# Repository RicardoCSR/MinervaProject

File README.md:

# MinervaProject

Registro Mestre de Projeto 

Bases e arquivos de apoio utilizados para o desenvolvimento do projeto:

STM32duino - IDE Arduino Ver.1 e Ver.2

- Fontes TTL 
https://github.com/FrankBoesing/fonts.git
- Display TFT SPI/I2C
https://github.com/Bodmer/TFT_eSPI
- FontConverter - 1
https://rop.nl/truetype2gfx/
- FontConverter - 2
https://oleddisplay.squix.ch/#/home
- RGB888 para RGB565
https://trolsoft.ru/ru/articles/rgb565-color-picker
- App (EM TESTE)
https://thunkable.com/#/

Nixie_Clock - Extensor de Sensores de Sobrevivência

Iniciando em 16/10/2021

Projeto Minerva da paixão pelos clássicos tubos Nixie desenvolvidos na década de 50 aos modernos display LCD, da inspiração veio junto o desafio de unir o antigo ao novo agregando diversos sensores para a apresentação de informações para uso e sobrevivência diário como:

- Pressão (mmHg)
- Temperatura (ºC e F)
- Umidade (%)
- Altitude
- sieverts (µSv e mSv)
- Hora/Data
- Calendário Completo
- Calculadora
- Grandezas e Medidas
- Estação do Ano (Primavera)
- Semana (Semana 39)
- Modo de ajustes dos parâmetros 

Sendo organizados pelos Menus:

Geiger                              - Apresenta Contagem por Segundo, Leitura Sieverts nSv/s
Dosimeter                           - Apresenta valor Dosimetro, Tempo de atualização, faixa de risco de Sv/h
Geiger GF                           - Apresenta gráfico dos valores apresentados nas 24 Horas do Geiger
Calendar                            - Apresenta Calendário
Timer                               - Apresenta Alarme, Contador e Tempo de Volta
Weather GF Temperature              - Apresenta gráfico dos valores apresentados nas 24 Horas do Temperatura
Weather GF Humidity                 - Apresenta gráfico dos valores apresentados nas 24 Horas do Umidade
Weather GF Atmosferic Pressure      - Apresenta gráfico dos valores apresentados nas 24 Horas do Pressão Atmosferica
Weather                             - Apresenta Temperatura, Umidade, Pressão Atmosférica, mínima e máxima e previsão via 
User                                - Apresenta Configurações básica de nome e imagem de Perfil
Calculator                          - Apresenta Calculadora de Operação Simples (Modendo ser extender a outros modelos)
Gerador de Sinais                   - Apresenta função de gerador de Sinais de 3.3V
Nixie Settings                      - Apresenta ajuste de animação Nixie
WiFi Settings                       - Apresenta Configurações de Acesso a rede externa
Settings                            - Apresenta Configurações de Ajuste da Tela

Database                            - Apresenta valores de todas as variaveis presentes (USO DESENVOLVIMENTO).

Componentes e suas caracteristicas

SN74141 : True Table // Podendo utilizar k155id1 ou SN74141
- D C B A #
- L, L, L, L 0
- L, L, L, H 1
- L, L, H, L 2
- L, L, H, H 3
- L, H, L, L 4
- L, H, L, H 5
- L, H, H, L 6
- L, H, H, H 7
- H, L, L, L 8
- H, L, L, H 9
- H, L, H, L N
- H, L, H, H N
- H, H, L, L N
- H, H, L, H N
- H, H, H, L N
- H, H, H, H N

ILI9486_DRIVER - Alimentação Ideal 3v3
TFT 8-BIT PARALLEL

Lista Terminais Utilizados STM32L476RG  29/08/2022

- R       Botao Hard Reset (Apenas para Desenvolvimento)

- PA0     TFT_RD
- PA1     TFT_WD
- PA2     
- PA3     
- PA4     TFT_DC
- PA5     
- PA6    
- PA7     
- PA8     TFT_D7
- PA9     TFT_D1
- PA10    TFT_D2
- PA11    
- PA12    
- PA15    

- PB0     TFT_CS
- PB1    
- PB2     
- PB3     TFT_D3
- PB4     TFT_D5
- PB5     TFT_D4
- PB6     
- PB7     
- PB8     
- PB9     
- PB10    TFT_D6
- PB12   
- PB13    
- PB14  
- PB15   

- PC0
- PC1     TFT_RST
- PC2
- PC3
- PC4
- PC5
- PC6
- PC7     TFT_D0
- PC8
- PC9
- PC10
- PC11
- PC12
- PC13   
- PC14    
- PC15    

- PD2

- PH0
- PH1

Lista Terminais Utilizados ESP32S  29/08/2022

- R       Botao Hard Reset

- GPIO0
- GPIO1
- GPIO2
- GPIO3
- GPIO4
- GPIO6
- GPIO7
- GPIO8
- GPIO9
- GPIO10
- GPIO11
- GPIO12
- GPIO13
- GPIO14
- GPIO15
- GPIO16
- GPIO17
- GPIO18
- GPIO19
- GPIO21
- GPIO22
- GPIO23
- GPIO25
- GPIO26
- GPIO27
- GPIO32
- GPIO33
- GPIO34
- GPIO35
- GPIO36
- GPIO39

*Projeto alterado para a Rev.3 sendo substituido o display ST7789 para o modelo ILI9486 de 480x320 em 8-Bit Paralelo pela velocidade de carregamento e estabilidade durante execuções e aplicações que envolvem banco de dados. O microcontrolador anterior STM32F401CCU6 substituido pelo modelo STM32L476RG de maior banda de memoria e expansão. Podendo ser substituido por um modelo mais economico.

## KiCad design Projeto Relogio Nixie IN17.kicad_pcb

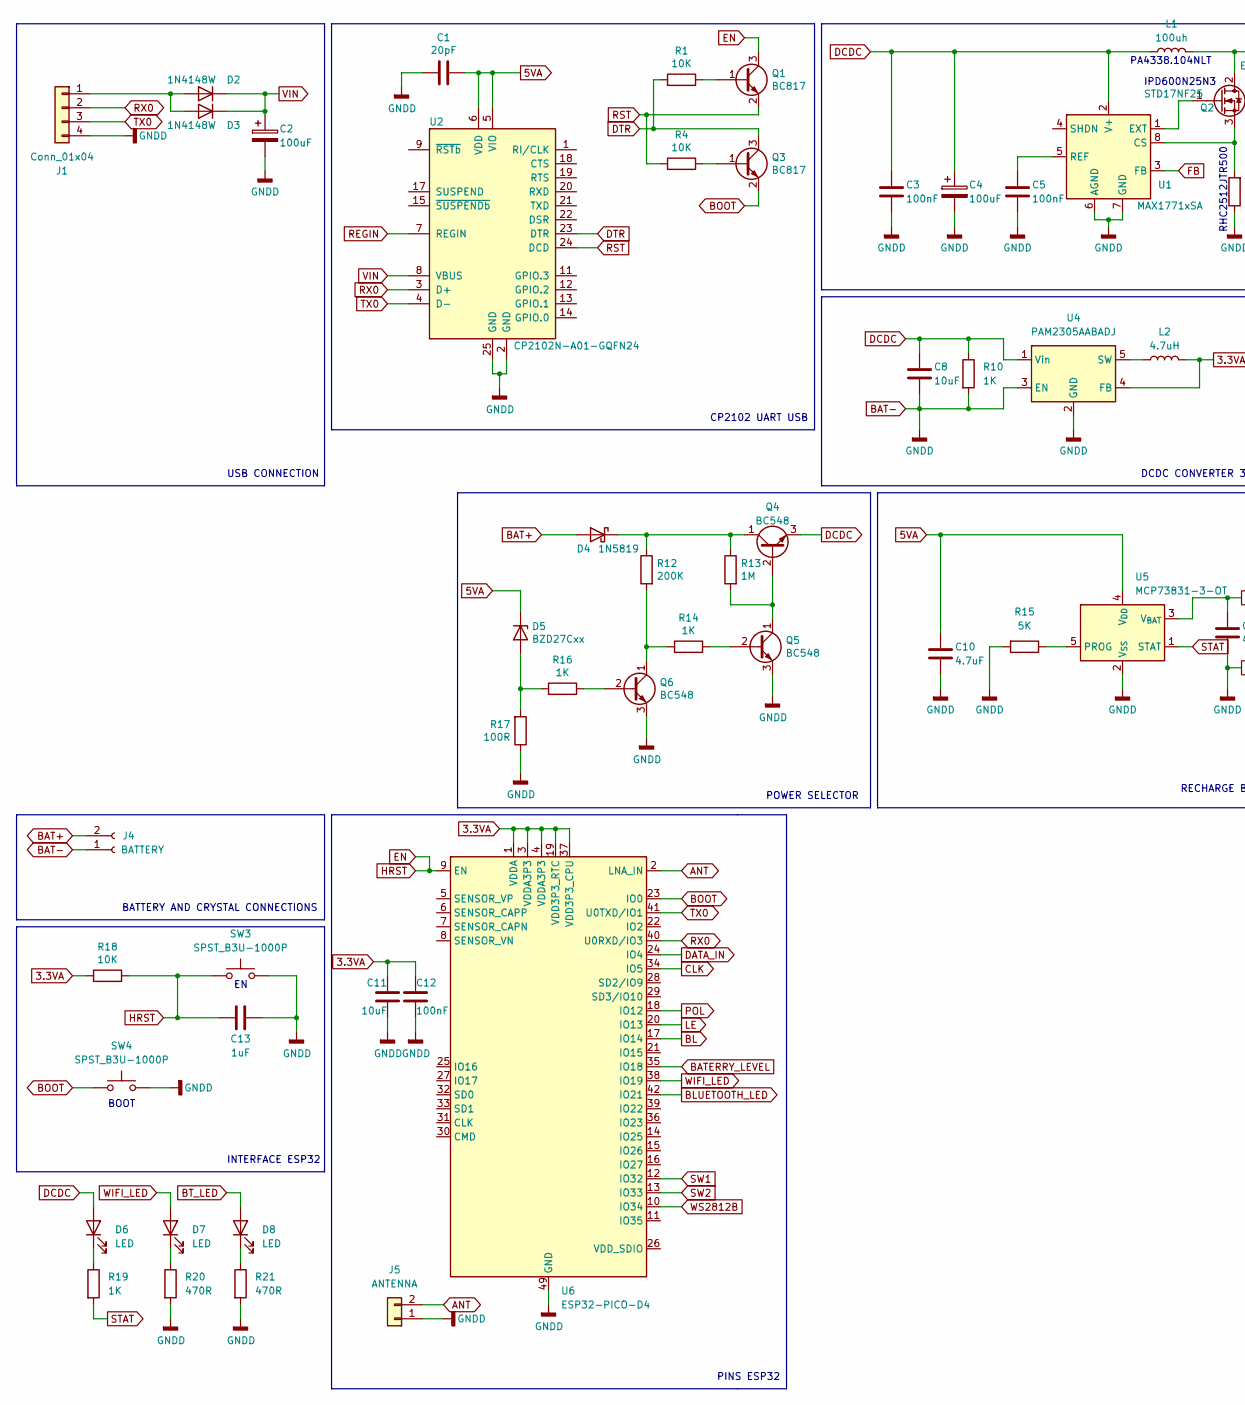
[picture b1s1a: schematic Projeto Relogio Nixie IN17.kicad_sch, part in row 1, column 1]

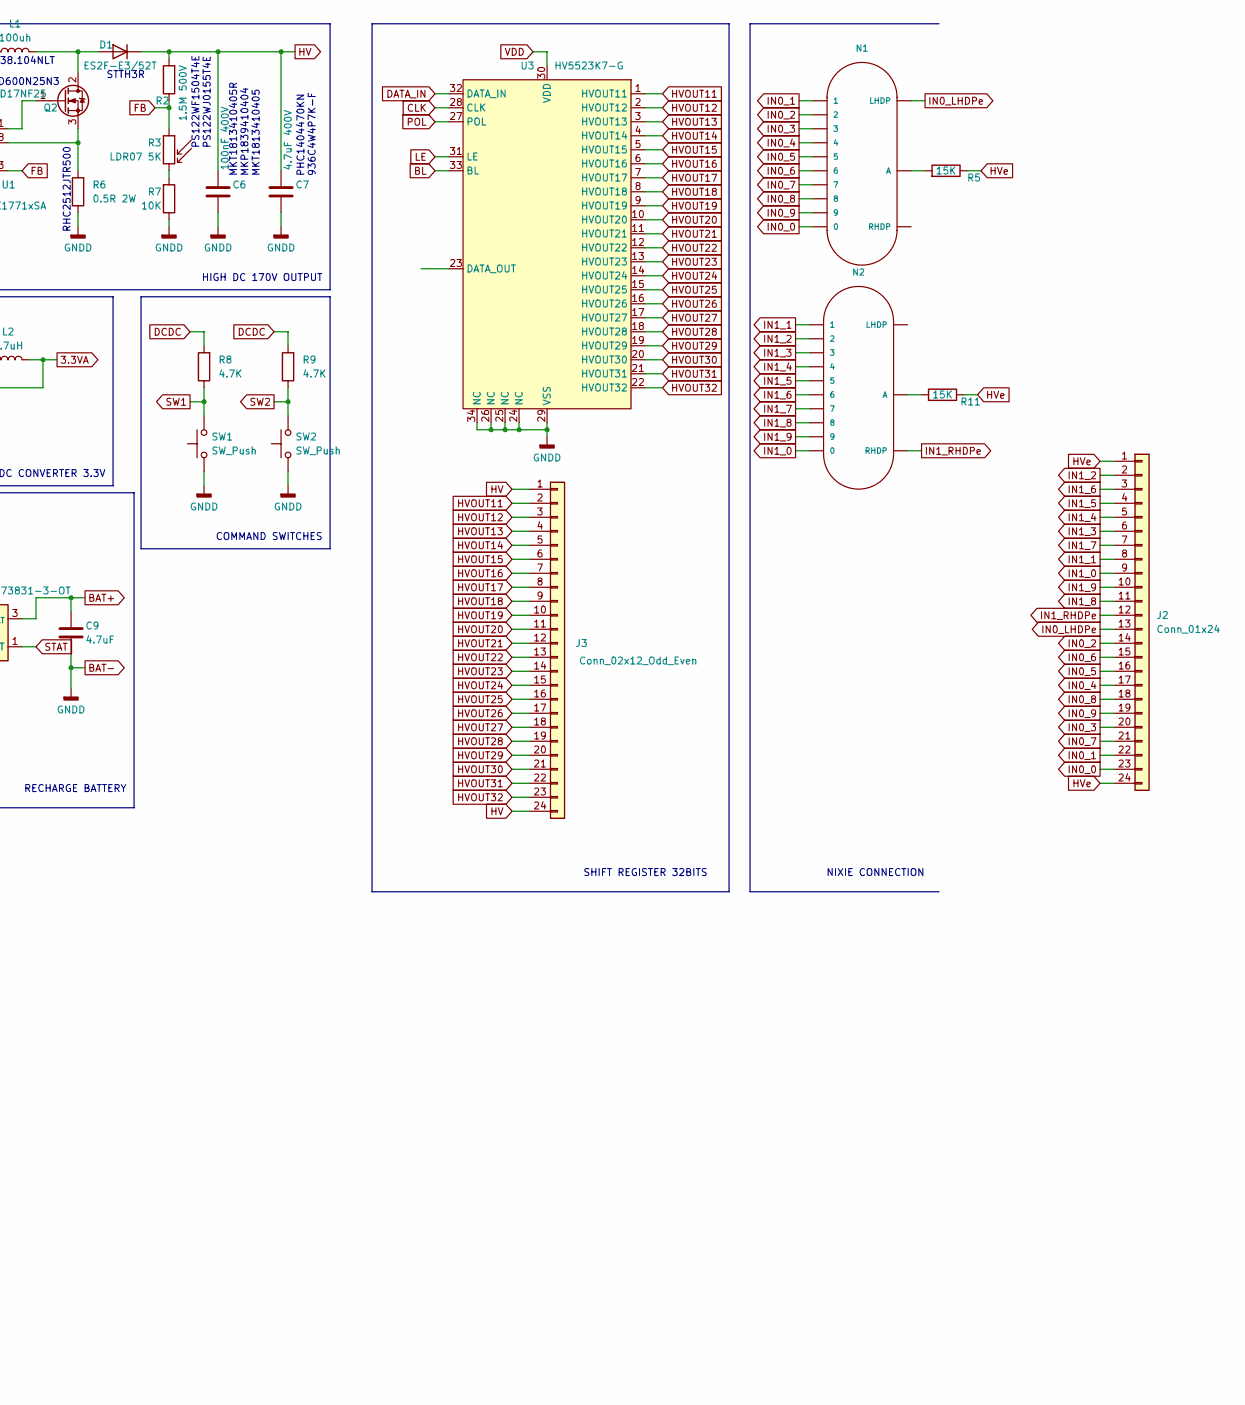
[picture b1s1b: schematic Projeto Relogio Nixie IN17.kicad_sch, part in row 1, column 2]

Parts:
C1: 20pF; C_0805_2012Metric
C2, C4: 100uF; CP_EIA-1608-08_AVX-J
C3, C5, C12: 100nF; C_0805_2012Metric
C6: 100nF 400V; C_Axial_L5.1mm_D3.1mm_P10.00mm_Horizontal
C7: 4.7uF 400V; C_Axial_L5.1mm_D3.1mm_P10.00mm_Horizontal
C8, C11: 10uF; C_0805_2012Metric
C9, C10: 4.7uF; C_0805_2012Metric
C13: 1uF; C_0805_2012Metric
D1: ES2F-E3/52T; D_SMB
D2, D3: 1N4148W; D_SOD-123
D4: 1N5819; D_0805_2012Metric
D5: BZD27Cxx; D_2114_3652Metric
D6, D7, D8: LED; LED_1206_3216Metric
J1: Conn_01x04; Magnetic_01x04
J2: Conn_01x24; TE_2-1734839-4_1x24-1MP_P0.5mm_Horizontal
J3: Conn_02x12_Odd_Even; TE_2-1734839-4_1x24-1MP_P0.5mm_Horizontal
J4: BATTERY; PinHeader_1x02_P2.00mm_Vertical
J5: ANTENNA; PinHeader_1x02_P2.00mm_Vertical
L1: 100uh; L_Bourns-SRN8040_8x8.15mm
L2: 4.7uH; L_Bourns_SRP5030T
N1, N2: IN-16; nixies-us-IN-16
Q1, Q3: BC817; SOT-23
Q2: STD17NF25; TO-252-2
Q4, Q5, Q6: BC548; SOT-23
R1, R4, R7, R18: 10K; R_0603_1608Metric
R2: 1.5M 500V; R_2512_6332Metric_Pad1.40x3.35mm_HandSolder
R3: LDR07 5K; R_LDR_5.1x4.3mm_P3.4mm_Vertical
R5, R11: 15K; R_0603_1608Metric
R6: 0.5R 2W; R_2512_6332Metric_Pad1.40x3.35mm_HandSolder
R8, R9: 4.7K; R_0603_1608Metric
R10, R14, R16, R19: 1K; R_0603_1608Metric
R12: 200K; R_0603_1608Metric
R13: 1M; R_0603_1608Metric
R15: 5K; R_0603_1608Metric
R17: 100R; R_0603_1608Metric
R20, R21: 470R; R_0603_1608Metric
SW1, SW2: SW_Push; PinHeader_1x02_P2.00mm_Vertical
SW3, SW4: SPST_B3U-1000P; SW_SPST_B3U-1000P
U1: MAX1771xSA; SO-8_3.9x4.9mm_P1.27mm
U2: CP2102N-A01-GQFN24; QFN-24-1EP_4x4mm_P0.5mm_EP2.6x2.6mm
U3: HV5523K7-G; QFN-44-1EP_7x7mm_P0.5mm_EP5.15x5.15mm
U4: PAM2305AABADJ; TSOT-23-5
U5: MCP73831-3-OT; SOT-23-5
U6: ESP32-PICO-D4; QFN-48-1EP_7x7mm_P0.5mm_EP5.3x5.3mm

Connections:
3.3VA: C11.1, C12.1, L2.2, R18.2, U4.4 (FB), U6.1 (VDDA), U6.3 (VDDA3P3), U6.4 (VDDA3P3), U6.19 (VDD3P3_RTC), U6.37 (VDD3P3_CPU)
5VA: C1.1, C10.1, D5.1 (K), U2.5 (VIO), U2.6 (VDD), U5.4 (V_{DD}); also elsewhere on the board
ANT: J5.2, U6.2 (LNA_IN)
BAT+: C9.1, D4.2 (A), J4.2, U5.3 (V_{BAT})
BAT-: C1.2, C2.2, C3.2, C4.2, C5.2, C6.2, C7.2, C8.2, C9.2, C10.2, C11.2, C12.2, C13.2, J1.4, J4.1, J5.1, Q5.3 (E), Q6.3 (E), R6.1, R7.1, R10.2, R15.2, R17.1, R20.2, R21.2, SW1.1, SW2.1, SW3.3 (B), SW3.4 (B), SW4.3 (B), SW4.4 (B), U1.6 (AGND), U1.7 (GND), U2.2 (GND), U2.25 (GND), U3.24 (NC), U3.25 (NC), U3.26 (NC), U3.29 (VSS), U3.34 (NC), U4.2 (GND), U4.3 (EN), U5.2 (V_{SS}), U6.49 (GND)
BATERRY_LEVEL: U6.35 (IO18)
BL: U3.33 (BL), U6.17 (IO14)
BLUETOOTH_LED: U6.42 (IO21)
BOOT: Q3.2 (E), SW4.1 (A), SW4.2 (A), U6.23 (IO0)
BT_LED: D8.2 (A)
CLK: U3.28 (CLK), U6.34 (IO5)
DATA_IN: U3.32 (DATA_IN), U6.24 (IO4)
DCDC: C3.1, C4.1, C8.1, D6.2 (A), L1.1, Q4.3 (E), R8.2, R9.2, R10.1, U1.2 (V+), U4.1 (Vin)
DTR: Q3.3 (C), R1.2, U2.23 (DTR)
EN: C13.1, Q1.3 (C), R18.1, SW3.1 (A), SW3.2 (A), U6.9 (EN)
FB: R2.1, R3.1, U1.3 (FB)
HV: C6.1, C7.1, D1.1 (K), J3.1, J3.24, R2.2
HVOUT11: J3.2, U3.1 (HVOUT11)
HVOUT12: J3.3, U3.2 (HVOUT12)
HVOUT13: J3.4, U3.3 (HVOUT13)
HVOUT14: J3.5, U3.4 (HVOUT14)
HVOUT15: J3.6, U3.5 (HVOUT15)
HVOUT16: J3.7, U3.6 (HVOUT16)
HVOUT17: J3.8, U3.7 (HVOUT17)
HVOUT18: J3.9, U3.8 (HVOUT18)
HVOUT19: J3.10, U3.9 (HVOUT19)
HVOUT20: J3.11, U3.10 (HVOUT20)
HVOUT21: J3.12, U3.11 (HVOUT21)
HVOUT22: J3.13, U3.12 (HVOUT22)
HVOUT23: J3.14, U3.13 (HVOUT23)
HVOUT24: J3.15, U3.14 (HVOUT24)
HVOUT25: J3.16, U3.15 (HVOUT25)
HVOUT26: J3.17, U3.16 (HVOUT26)
HVOUT27: J3.18, U3.17 (HVOUT27)
HVOUT28: J3.19, U3.18 (HVOUT28)
HVOUT29: J3.20, U3.19 (HVOUT29)
HVOUT30: J3.21, U3.20 (HVOUT30)
HVOUT31: J3.22, U3.21 (HVOUT31)
HVOUT32: J3.23, U3.22 (HVOUT32)
HVe: J2.1, J2.24, R5.1, R11.1
IN0_0: J2.23, N1.0
IN0_1: J2.22, N1.1
IN0_2: J2.14, N1.2
IN0_3: J2.20, N1.3
IN0_4: J2.17, N1.4
IN0_5: J2.16, N1.5
IN0_6: J2.15, N1.6
IN0_7: J2.21, N1.7
IN0_8: J2.18, N1.8
IN0_9: J2.19, N1.9
IN0_LHDPe: J2.13, N1.LHDP
IN1_0: J2.9, N2.0
IN1_1: J2.8, N2.1
IN1_2: J2.2, N2.2
IN1_3: J2.6, N2.3
IN1_4: J2.5, N2.4
IN1_5: J2.4, N2.5
IN1_6: J2.3, N2.6
IN1_7: J2.7, N2.7
IN1_8: J2.11, N2.8
IN1_9: J2.10, N2.9
IN1_RHDPe: J2.12, N2.RHDP
LE: U3.31 (LE), U6.20 (IO13)
unnamed: D1.2 (A), L1.2, Q2.2 (D)
unnamed: D2.2 (A), D3.2 (A), J1.1
unnamed: D4.1 (K), Q4.1 (C), R12.1, R13.1
unnamed: D5.2 (A), R16.2, R17.2
unnamed: D6.1 (K), R19.1
unnamed: D7.1 (K), R20.1
unnamed: D8.1 (K), R21.1
unnamed: N1.A, R5.2
unnamed: N2.A, R11.2
unnamed: Q1.1 (B), R1.1
unnamed: Q2.1 (G), U1.1 (EXT)
unnamed: Q2.3 (S), R6.2, U1.8 (CS)
unnamed: Q3.1 (B), R4.1
unnamed: Q4.2 (B), Q5.1 (C), R13.2
unnamed: Q5.2 (B), R14.1
unnamed: Q6.2 (B), R16.1
unnamed: Q6.1 (C), R12.2, R14.2
unnamed: R3.2, R7.2
unnamed: C5.1, U1.5 (REF)
unnamed: L2.1, U4.5 (SW)
unnamed: R15.1, U5.5 (PROG)
POL: U3.27 (POL), U6.18 (IO12)
REGIN: U2.7 (REGIN)
RST: Q1.2 (E), R4.2, U2.24 (DCD)
RX0: J1.2, U2.3 (D+), U6.40 (U0RXD/IO3)
STAT: R19.2, U5.1 (STAT)
SW1: R8.1, SW1.2, U6.12 (IO32)
SW2: R9.1, SW2.2, U6.13 (IO33)
TX0: J1.3, U2.4 (D-), U6.41 (U0TXD/IO1)
VDD: U3.30 (VDD)
VIN: C2.1, D2.1 (K), D3.1 (K), U2.8 (VBUS); also elsewhere on the board
WIFI_LED: D7.2 (A), U6.38 (IO19)
WS2812B: U6.10 (IO34)

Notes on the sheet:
CP2102 UART USB
POWER SELECTOR
COMMAND SWITCHES
PA4338.104NLT
PHC1404470KN 936C4W4P7K-F
RHC2512JTR500
INTERFACE ESP32
DCDC CONVERTER 3.3V
IPD600N25N3
HIGH DC 170V OUTPUT
BATTERY AND CRYSTAL CONNECTIONS
BOOT
PINS ESP32
USB CONNECTION
STTH3R
SHIFT REGISTER 32BITS
NIXIE CONNECTION
PS122WF1504T4E PS122WJ0155T4E
RECHARGE BATTERY
MKT1813410405R MKP1839410404 MKT1813410405

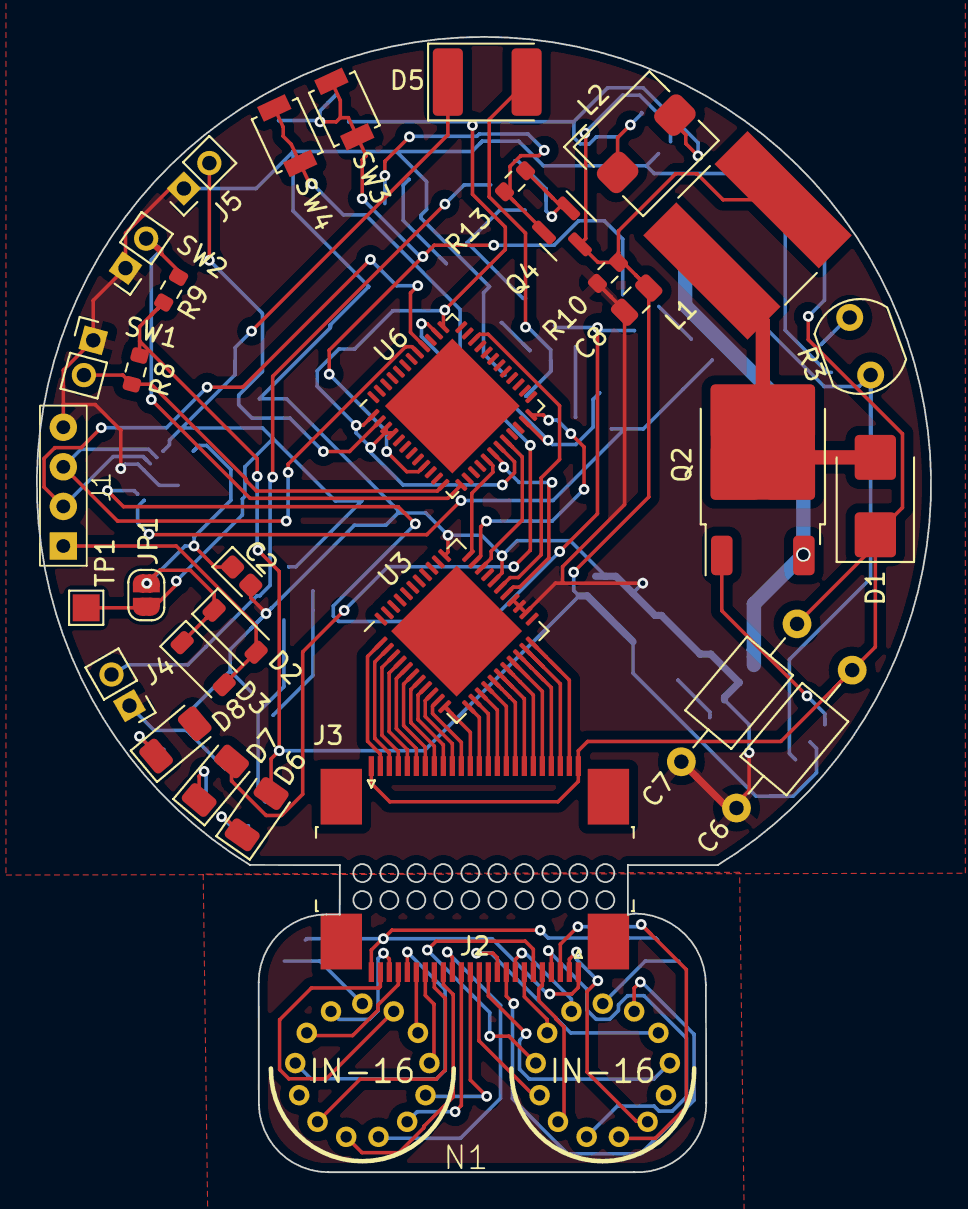
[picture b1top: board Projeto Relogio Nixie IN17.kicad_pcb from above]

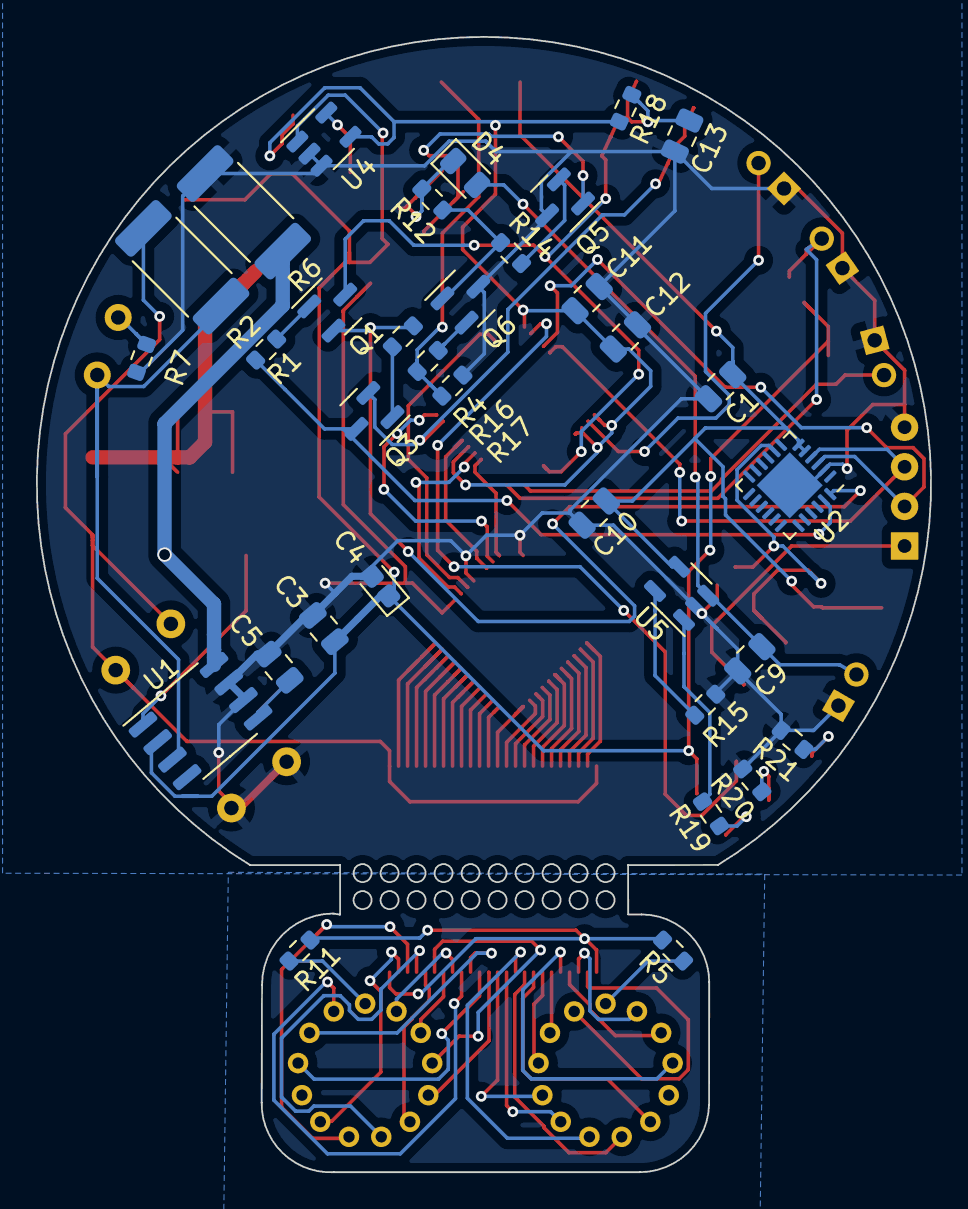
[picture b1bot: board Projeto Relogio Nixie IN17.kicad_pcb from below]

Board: 2 copper layers, 49.7 x 63.1 mm, 69 parts (34 on the bottom side), 90 nets.

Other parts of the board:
JP1: SolderJumper-2_P1.3mm_Open_RoundedPad1.0x1.5mm
TP1: 5VA; TestPoint_Pad_1.5x1.5mm

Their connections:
5VA: JP1.2 (B), TP1.1; also elsewhere on the board
VIN: JP1.1 (A); also elsewhere on the board

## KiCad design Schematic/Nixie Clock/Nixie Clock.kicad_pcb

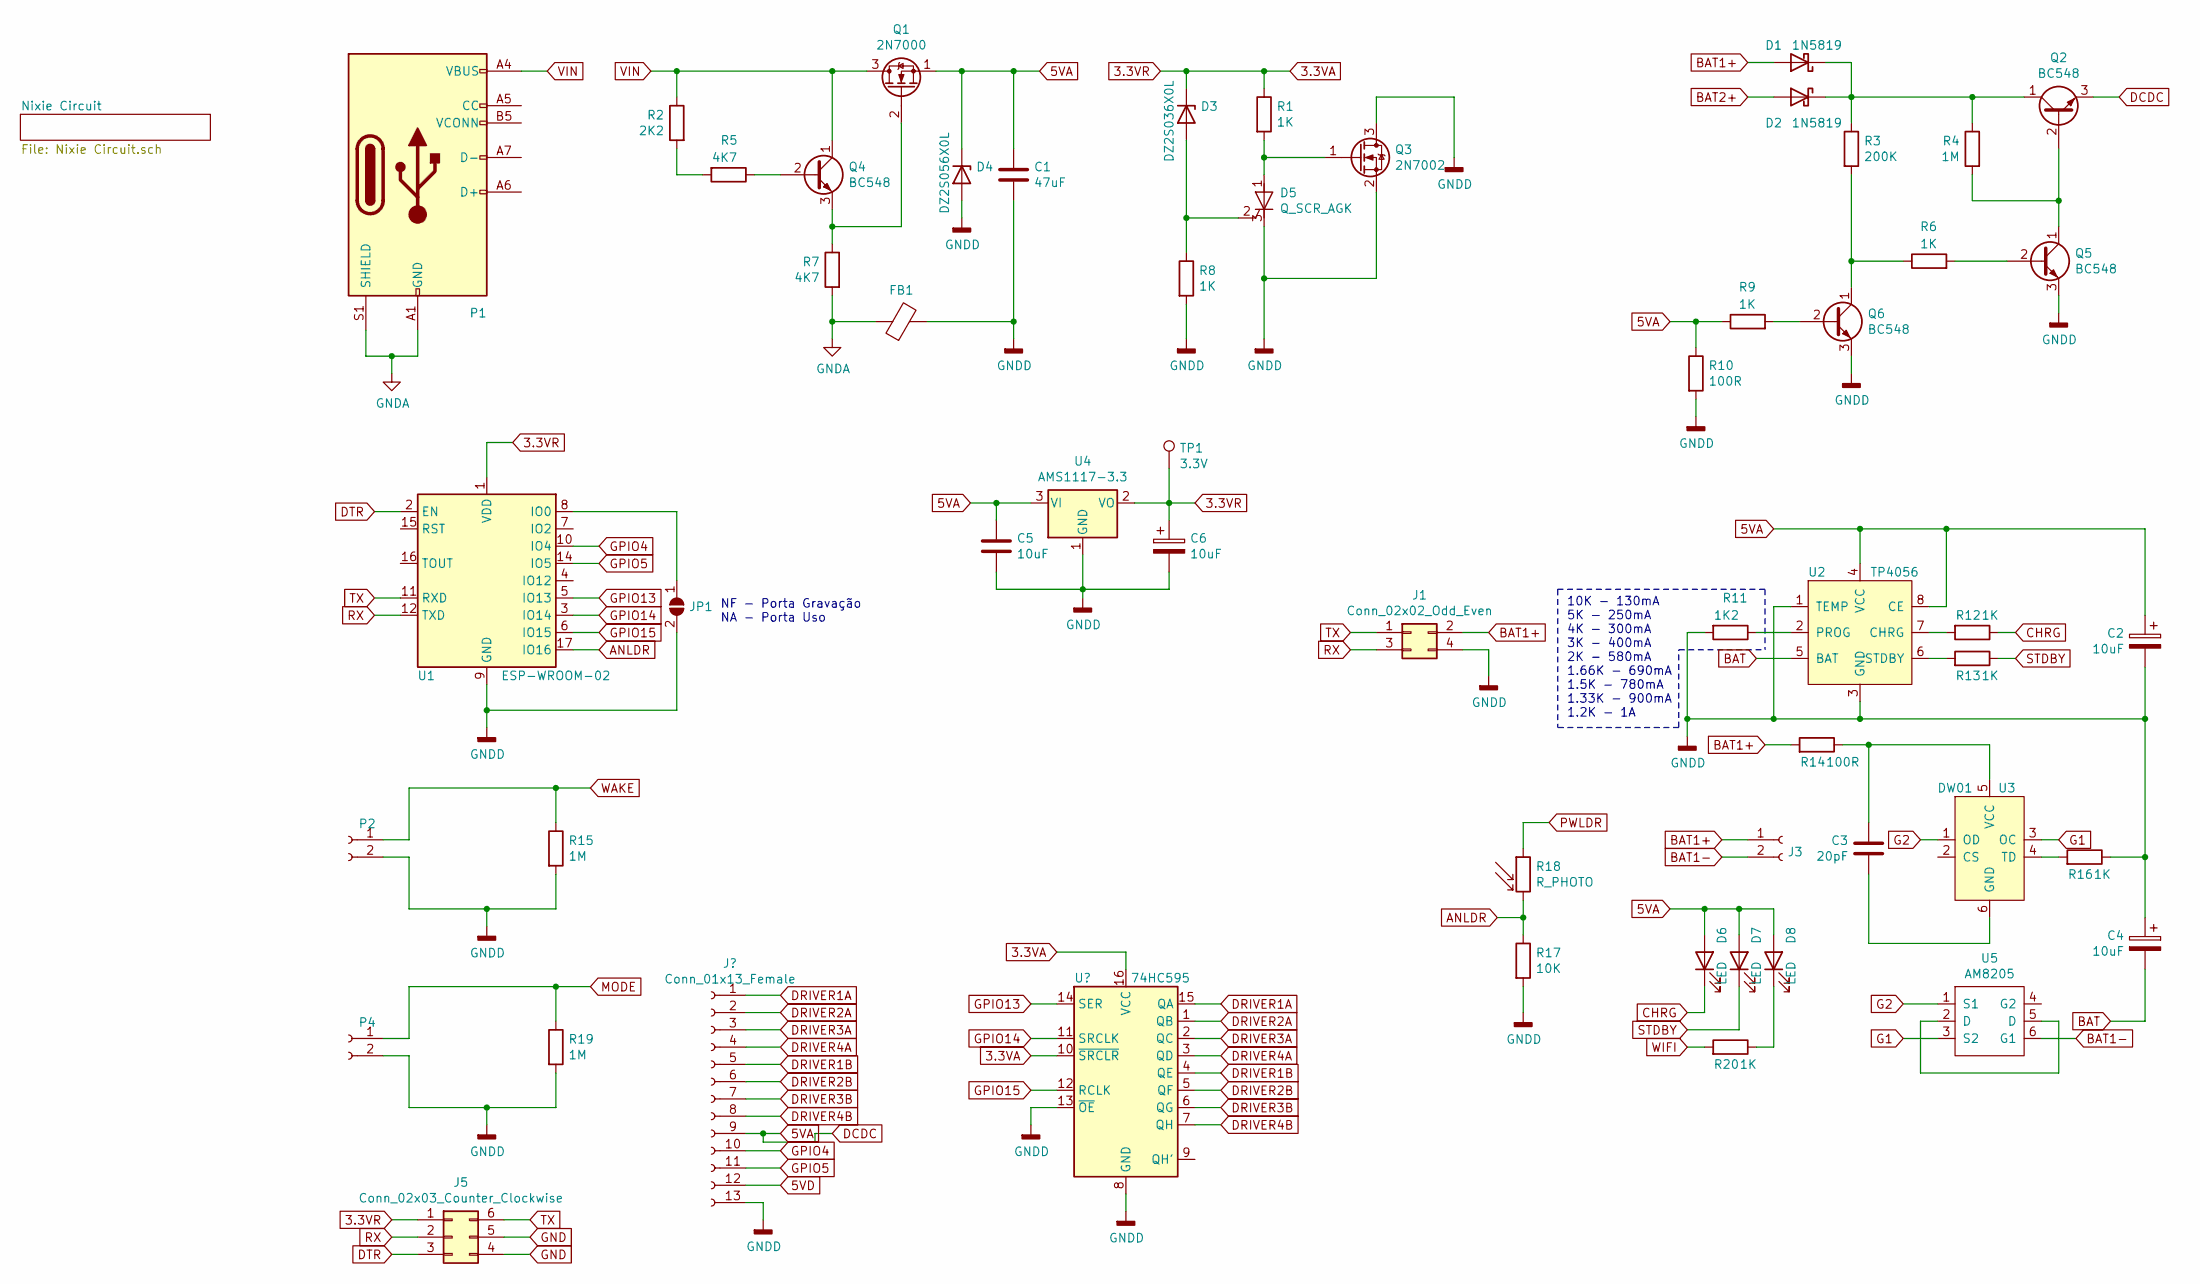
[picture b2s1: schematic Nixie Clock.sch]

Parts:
C1: 47uF; C_0805_2012Metric_Pad1.15x1.40mm_HandSolder
C2, C4, C5, C6: 10uF; C_0805_2012Metric_Pad1.15x1.40mm_HandSolder
C3: 20pF; C_0805_2012Metric_Pad1.15x1.40mm_HandSolder
D1, D2: 1N5819; D_SOD-523
D3: DZ2S036X0L; D_SOD-523
D4: DZ2S056X0L; D_SOD-523
D5: Q_SCR_AGK; SOT-23
D6, D7, D8: LED; R_0805_2012Metric
FB1: Ferrite_Bead; R_0201_0603Metric_Pad0.64x0.40mm_HandSolder
J1: Conn_02x02_Odd_Even; Molex_Nano-Fit_105310-xx04_2x02_P2.50mm_Vertical
J3: Conn_01x02_Female; PinHeader_1x02_P2.00mm_Vertical
J5: Conn_02x03_Counter_Clockwise; PinHeader_2x03_P2.00mm_Vertical
JP1: SolderJumper_2_Open; SolderJumper-2_P1.3mm_Open_RoundedPad1.0x1.5mm
P1: USB_C_Plug_USB2.0; USB_C_Receptacle_XKB_U262-16XN-4BVC11
P2, P4: Conn_01x02_Female; PinHeader_1x02_P2.00mm_Vertical
Q1: 2N7000; SOT-23
Q2, Q4, Q5, Q6: BC548; SOT-23
Q3: 2N7002; SOT-23
R1, R6, R8, R9, R12, R13, R16, R20: 1K; R_0201_0603Metric_Pad0.64x0.40mm_HandSolder
R2: 2K2; R_0201_0603Metric_Pad0.64x0.40mm_HandSolder
R3: 200K; R_0201_0603Metric_Pad0.64x0.40mm_HandSolder
R4, R15, R19: 1M; R_0201_0603Metric_Pad0.64x0.40mm_HandSolder
R5, R7: 4K7; R_0201_0603Metric_Pad0.64x0.40mm_HandSolder
R10, R14: 100R; R_0201_0603Metric_Pad0.64x0.40mm_HandSolder
R11: 1K2; R_0201_0603Metric_Pad0.64x0.40mm_HandSolder
R17: 10K; R_0201_0603Metric_Pad0.64x0.40mm_HandSolder
R18: R_PHOTO; PinHeader_1x02_P2.00mm_Vertical
TP1: 3.3V; TestPoint_Pad_1.5x1.5mm
U1: ESP-WROOM-02; ESP-12E
U2: TP4056; MSOP-8-1EP_3x3mm_P0.65mm_EP1.95x2.15mm
U3: DW01; SOT-23-6
U4: AMS1117-3.3; SOT-223-3_TabPin2
U5: AM8205; TSSOP-8_3x3mm_P0.65mm

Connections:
3.3VA: C6.1, D3.1 (K), J5.1, R1.1, TP1.1, U1.1 (VDD), U4.2 (VO); also elsewhere on the board
5VA: C1.1, C2.1, C5.1, D4.1 (K), D6.2 (A), D7.2 (A), D8.2 (A), Q1.1 (S), Q2.3 (E), R9.1, R10.1, U2.4 (VCC), U2.8 (CE), U4.3 (VI); also elsewhere on the board
ANLDR: R17.1, R18.2, U1.17 (IO16)
BAT: C4.2, U2.5 (BAT)
BAT1+: D1.2 (A), J1.2, J3.1, R14.2
BAT1-: J3.2, U5.6 (G1)
BAT2+: D2.2 (A)
CHRG: D6.1 (K), R12.1
DTR: J5.3, U1.2 (EN)
G1: U3.3 (OC), U5.3 (S2)
G2: U3.1 (OD), U5.1 (S1)
GND: J5.4, J5.5
GNDA: FB1.1, P1.A1 (GND), P1.A12 (GND), P1.B1 (GND), P1.B12 (GND), P1.S1 (SHIELD), R7.2
GNDD: C1.2, C2.2, C4.1, C5.2, C6.2, D4.2 (A), D5.3 (K), FB1.2, J1.4, JP1.2 (B), P2.2, P4.2, Q3.2 (S), Q3.3 (D), Q5.3 (E), Q6.3 (E), R8.2, R10.2, R11.2, R15.2, R16.1, R17.2, R19.2, U1.9 (GND), U1.13 (GND), U1.18 (GND), U1.19 (GND), U2.1 (TEMP), U2.3 (GND), U4.1 (GND); also elsewhere on the board
GPIO4: U1.10 (IO4); also elsewhere on the board
GPIO5: U1.14 (IO5); also elsewhere on the board
GPIO13: U1.5 (IO13); also elsewhere on the board
GPIO14: U1.3 (IO14); also elsewhere on the board
GPIO15: U1.6 (IO15); also elsewhere on the board
MODE: P4.1, R19.1
unnamed: C3.1, R14.1, U3.5 (VCC)
unnamed: C3.2, U3.6 (GND)
unnamed: D1.1 (K), D2.1 (K), Q2.1 (C), R3.1, R4.1
unnamed: D3.2 (A), D5.2 (G), R8.1
unnamed: D5.1 (A), Q3.1 (G), R1.2
unnamed: D8.1 (K), R20.1
unnamed: JP1.1 (A), U1.8 (IO0)
unnamed: Q1.2 (G), Q4.3 (E), R7.1
unnamed: Q2.2 (B), Q5.1 (C), R4.2
unnamed: Q4.2 (B), R5.1
unnamed: Q5.2 (B), R6.2
unnamed: Q6.1 (C), R3.2, R6.1
unnamed: Q6.2 (B), R9.2
unnamed: R2.2, R5.2
unnamed: R11.1, U2.2 (PROG)
unnamed: R12.2, U2.7 (CHRG)
unnamed: R13.2, U2.6 (STDBY)
unnamed: R16.2, U3.4 (TD)
unnamed: U5.2 (D), U5.5 (D)
PWLDR: R18.1
RX: J1.3, J5.2, U1.12 (TXD)
STDBY: D7.1 (K), R13.1
TX: J1.1, J5.6, U1.11 (RXD)
VIN: P1.A4 (VBUS), P1.A9 (VBUS), P1.B4 (VBUS), P1.B9 (VBUS), Q1.3 (D), Q4.1 (C), R2.1
WAKE: P2.1, R15.1
WIFI: R20.2

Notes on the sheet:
NF - Porta Gravação NA - Porta Uso
10K - 130mA 5K - 250mA 4K - 300mA 3K - 400mA 2K - 580mA 1.66K - 690mA 1.5K - 780mA 1.33K - 900mA 1.2K - 1A

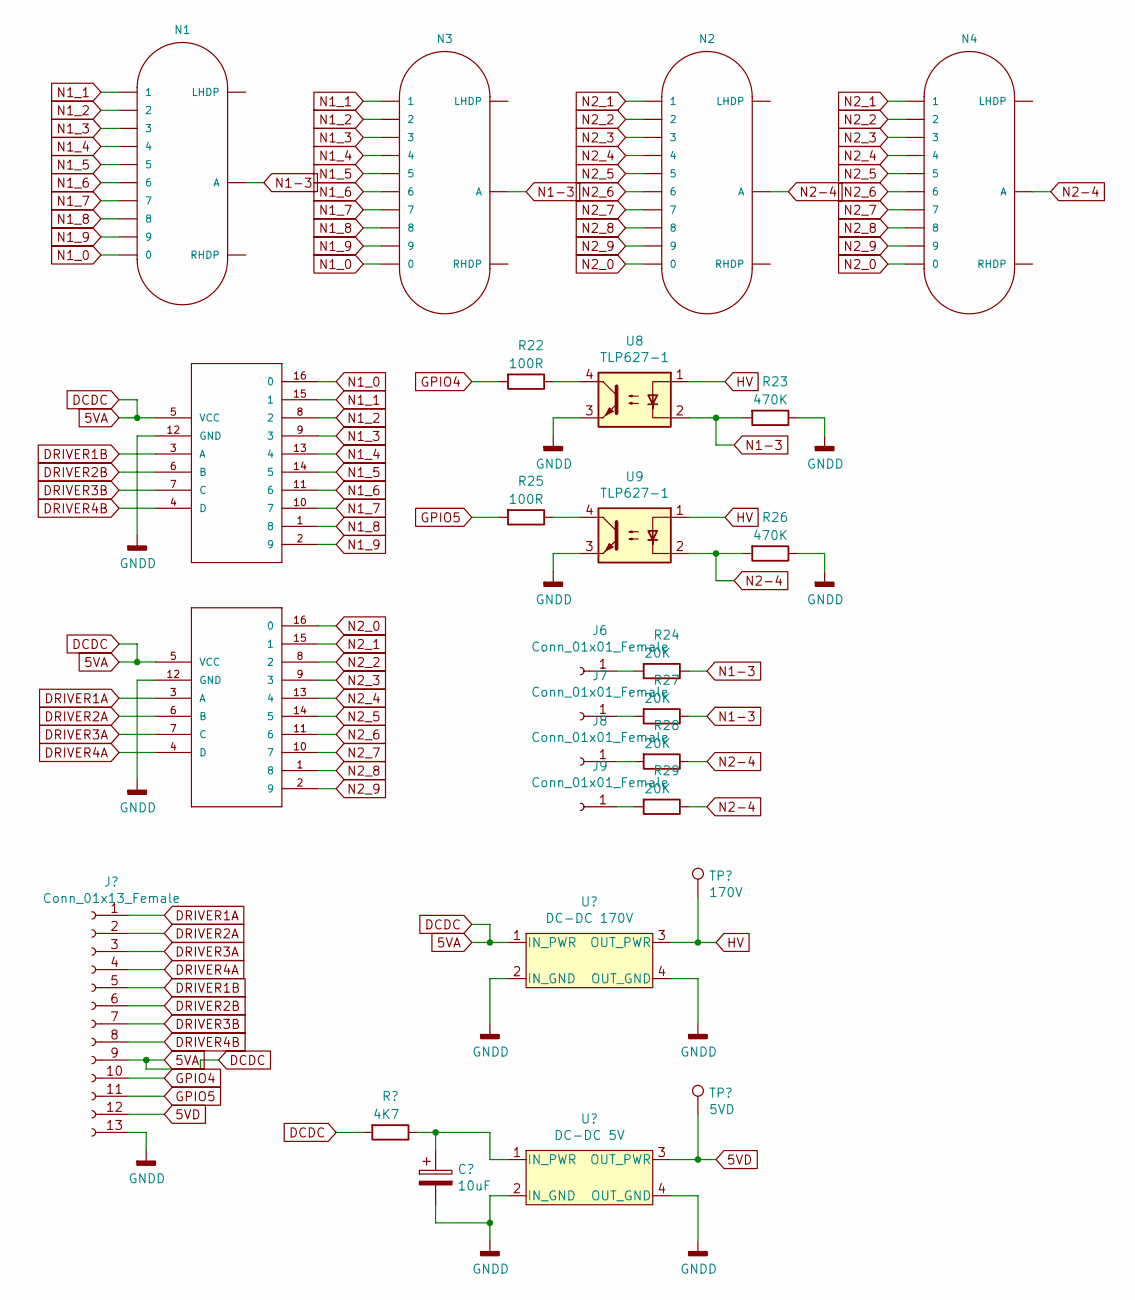
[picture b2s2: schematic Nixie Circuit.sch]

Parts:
J6, J7, J8, J9: Conn_01x01_Female; PinHeader_1x01_P2.00mm_Vertical
M1, M2: 74141DIP16; DIP-16_W7.62mm
N1, N2, N3, N4: IN-16; PinHeader_2x06_P2.00mm_Vertical
R22, R25: 100R; R_0201_0603Metric_Pad0.64x0.40mm_HandSolder
R23, R26: 470K; R_0201_0603Metric_Pad0.64x0.40mm_HandSolder
R24, R27, R28, R29: 20K; R_0201_0603Metric_Pad0.64x0.40mm_HandSolder
U8, U9: TLP627-1; SOP-4_3.8x4.1mm_P2.54mm

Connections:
5VA: M1.5 (VCC), M2.5 (VCC); also elsewhere on the board
DRIVER1A: M1.3 (A); also elsewhere on the board
DRIVER1B: M2.3 (A); also elsewhere on the board
DRIVER2A: M1.6 (B); also elsewhere on the board
DRIVER2B: M2.6 (B); also elsewhere on the board
DRIVER3A: M1.7 (C); also elsewhere on the board
DRIVER3B: M2.7 (C); also elsewhere on the board
DRIVER4A: M1.4 (D); also elsewhere on the board
DRIVER4B: M2.4 (D); also elsewhere on the board
GNDD: M1.12 (GND), M2.12 (GND), R23.1, R26.1, U8.3, U9.3; also elsewhere on the board
GPIO4: R22.2; also elsewhere on the board
GPIO5: R25.2; also elsewhere on the board
HV: U8.1, U9.1; also elsewhere on the board
N1-3: N1.A, N3.A, R23.2, R24.1, R27.1, U8.2
N1_0: M2.16 (0), N1.0, N3.0; also elsewhere on the board
N1_1: M2.15 (1), N1.1, N3.1; also elsewhere on the board
N1_2: M2.8 (2), N1.2, N3.2; also elsewhere on the board
N1_3: M2.9 (3), N1.3, N3.3; also elsewhere on the board
N1_4: M2.13 (4), N1.4, N3.4; also elsewhere on the board
N1_5: M2.14 (5), N1.5, N3.5; also elsewhere on the board
N1_6: M2.11 (6), N1.6, N3.6; also elsewhere on the board
N1_7: M2.10 (7), N1.7, N3.7; also elsewhere on the board
N1_8: M2.1 (8), N1.8, N3.8; also elsewhere on the board
N1_9: M2.2 (9), N1.9, N3.9; also elsewhere on the board
N2-4: N2.A, N4.A, R26.2, R28.1, R29.1, U9.2
N2_0: M1.16 (0), N2.0, N4.0; also elsewhere on the board
N2_1: M1.15 (1), N2.1, N4.1; also elsewhere on the board
N2_2: M1.8 (2), N2.2, N4.2; also elsewhere on the board
N2_3: M1.9 (3), N2.3, N4.3; also elsewhere on the board
N2_4: M1.13 (4), N2.4, N4.4; also elsewhere on the board
N2_5: M1.14 (5), N2.5, N4.5; also elsewhere on the board
N2_6: M1.11 (6), N2.6, N4.6; also elsewhere on the board
N2_7: M1.10 (7), N2.7, N4.7; also elsewhere on the board
N2_8: M1.1 (8), N2.8, N4.8; also elsewhere on the board
N2_9: M1.2 (9), N2.9, N4.9; also elsewhere on the board
unnamed: J6.1, R24.2
unnamed: J7.1, R27.2
unnamed: J8.1, R28.2
unnamed: J9.1, R29.2
unnamed: R22.1, U8.4
unnamed: R25.1, U9.4

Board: 2 copper layers, 85 parts (0 on the bottom side), 82 nets, no tracks yet.

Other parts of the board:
C7: 10uF; C_0805_2012Metric_Pad1.15x1.40mm_HandSolder
J2, J4, J10, J11: Conn_01x10_Female; PinHeader_1x10_P2.00mm_Vertical
R21: 4K7; R_0201_0603Metric_Pad0.64x0.40mm_HandSolder
TP2: 170V; TestPoint_Pad_1.5x1.5mm
TP3: 5VD; TestPoint_Pad_1.5x1.5mm
U6: DC-DC 170V; DCDC_2.5V_170V
U7: DC-DC 5V; DCDC_2V~5V
U10: 74HC595; DIP-16_W7.62mm

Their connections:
3.3VA: U10.10, U10.16; also elsewhere on the board
5VA: R21.2, U6.1; also elsewhere on the board
5VD: TP3.1, U7.3
DRIVER1A: U10.15; also elsewhere on the board
DRIVER1B: U10.4; also elsewhere on the board
DRIVER2A: U10.1; also elsewhere on the board
DRIVER2B: U10.5; also elsewhere on the board
DRIVER3A: U10.2; also elsewhere on the board
DRIVER3B: U10.6; also elsewhere on the board
DRIVER4A: U10.3; also elsewhere on the board
DRIVER4B: U10.7; also elsewhere on the board
GNDD: C7.2, U6.2, U6.4, U7.2, U7.4, U10.8, U10.13; also elsewhere on the board
GPIO13: U10.14; also elsewhere on the board
GPIO14: U10.11; also elsewhere on the board
GPIO15: U10.12; also elsewhere on the board
HV: TP2.1, U6.3; also elsewhere on the board
N1_0: J10.1; also elsewhere on the board
N1_1: J10.2; also elsewhere on the board
N1_2: J10.3; also elsewhere on the board
N1_3: J10.4; also elsewhere on the board
N1_4: J10.5; also elsewhere on the board
N1_5: J10.6; also elsewhere on the board
N1_6: J10.7; also elsewhere on the board
N1_7: J10.8; also elsewhere on the board
N1_8: J10.9; also elsewhere on the board
N1_9: J10.10; also elsewhere on the board
N2_0: J11.1; also elsewhere on the board
N2_1: J11.2; also elsewhere on the board
N2_2: J11.3; also elsewhere on the board
N2_3: J11.4; also elsewhere on the board
N2_4: J11.5; also elsewhere on the board
N2_5: J11.6; also elsewhere on the board
N2_6: J11.7; also elsewhere on the board
N2_7: J11.8; also elsewhere on the board
N2_8: J11.9; also elsewhere on the board
N2_9: J11.10; also elsewhere on the board
unnamed: C7.1, R21.1, U7.1
